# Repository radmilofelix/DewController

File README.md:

# DewController
 **Device to control the dew heaters and fans on astronomic instruments**
 
 Dew is an obvious nuisance for astronomic instruments and a simple way of getting rid of it are heaters placed on elements of the optical chain susceptible to forming dew.

The described device is a 6 channel heater driver, and a 2 channel fan driver, as some reflecting telescopes have a fan installed on the back of the main mirror.

The heaters and fans are driven by PWM signals software controlled by means of a STM32F103 microcontroller. The connection with the computer can be achieved either through USB or Ethernet (TCP/IP) or both.

The device also has a DHT22 temperature & humidity sensor, so the dew point can be computed to get an indication of whether the heaters have to be powered and how much power has to be supplied to the heaters.

# Description

1.  - Heater 1 (connector and LED)
2.  - Heater 2 (connector and LED)
3.  - Heater 3 (connector and LED)
4.  - Heater 4 (connector and LED)
5.  - Heater 5 (connector and LED)
6.  - Heater 6 (connector and LED)
7.  - USB connector
8.  - Ethernet Connector
9.  - Connector for servicing - 9 pin
10.  - Fan 1 (connector and LED)
11.  - Fan 2 (connector and LED)
12. - DHT 22 sensor
13. - 12V power connector
14. - Reset button
15. - Bracket for mounting the device on the telescope

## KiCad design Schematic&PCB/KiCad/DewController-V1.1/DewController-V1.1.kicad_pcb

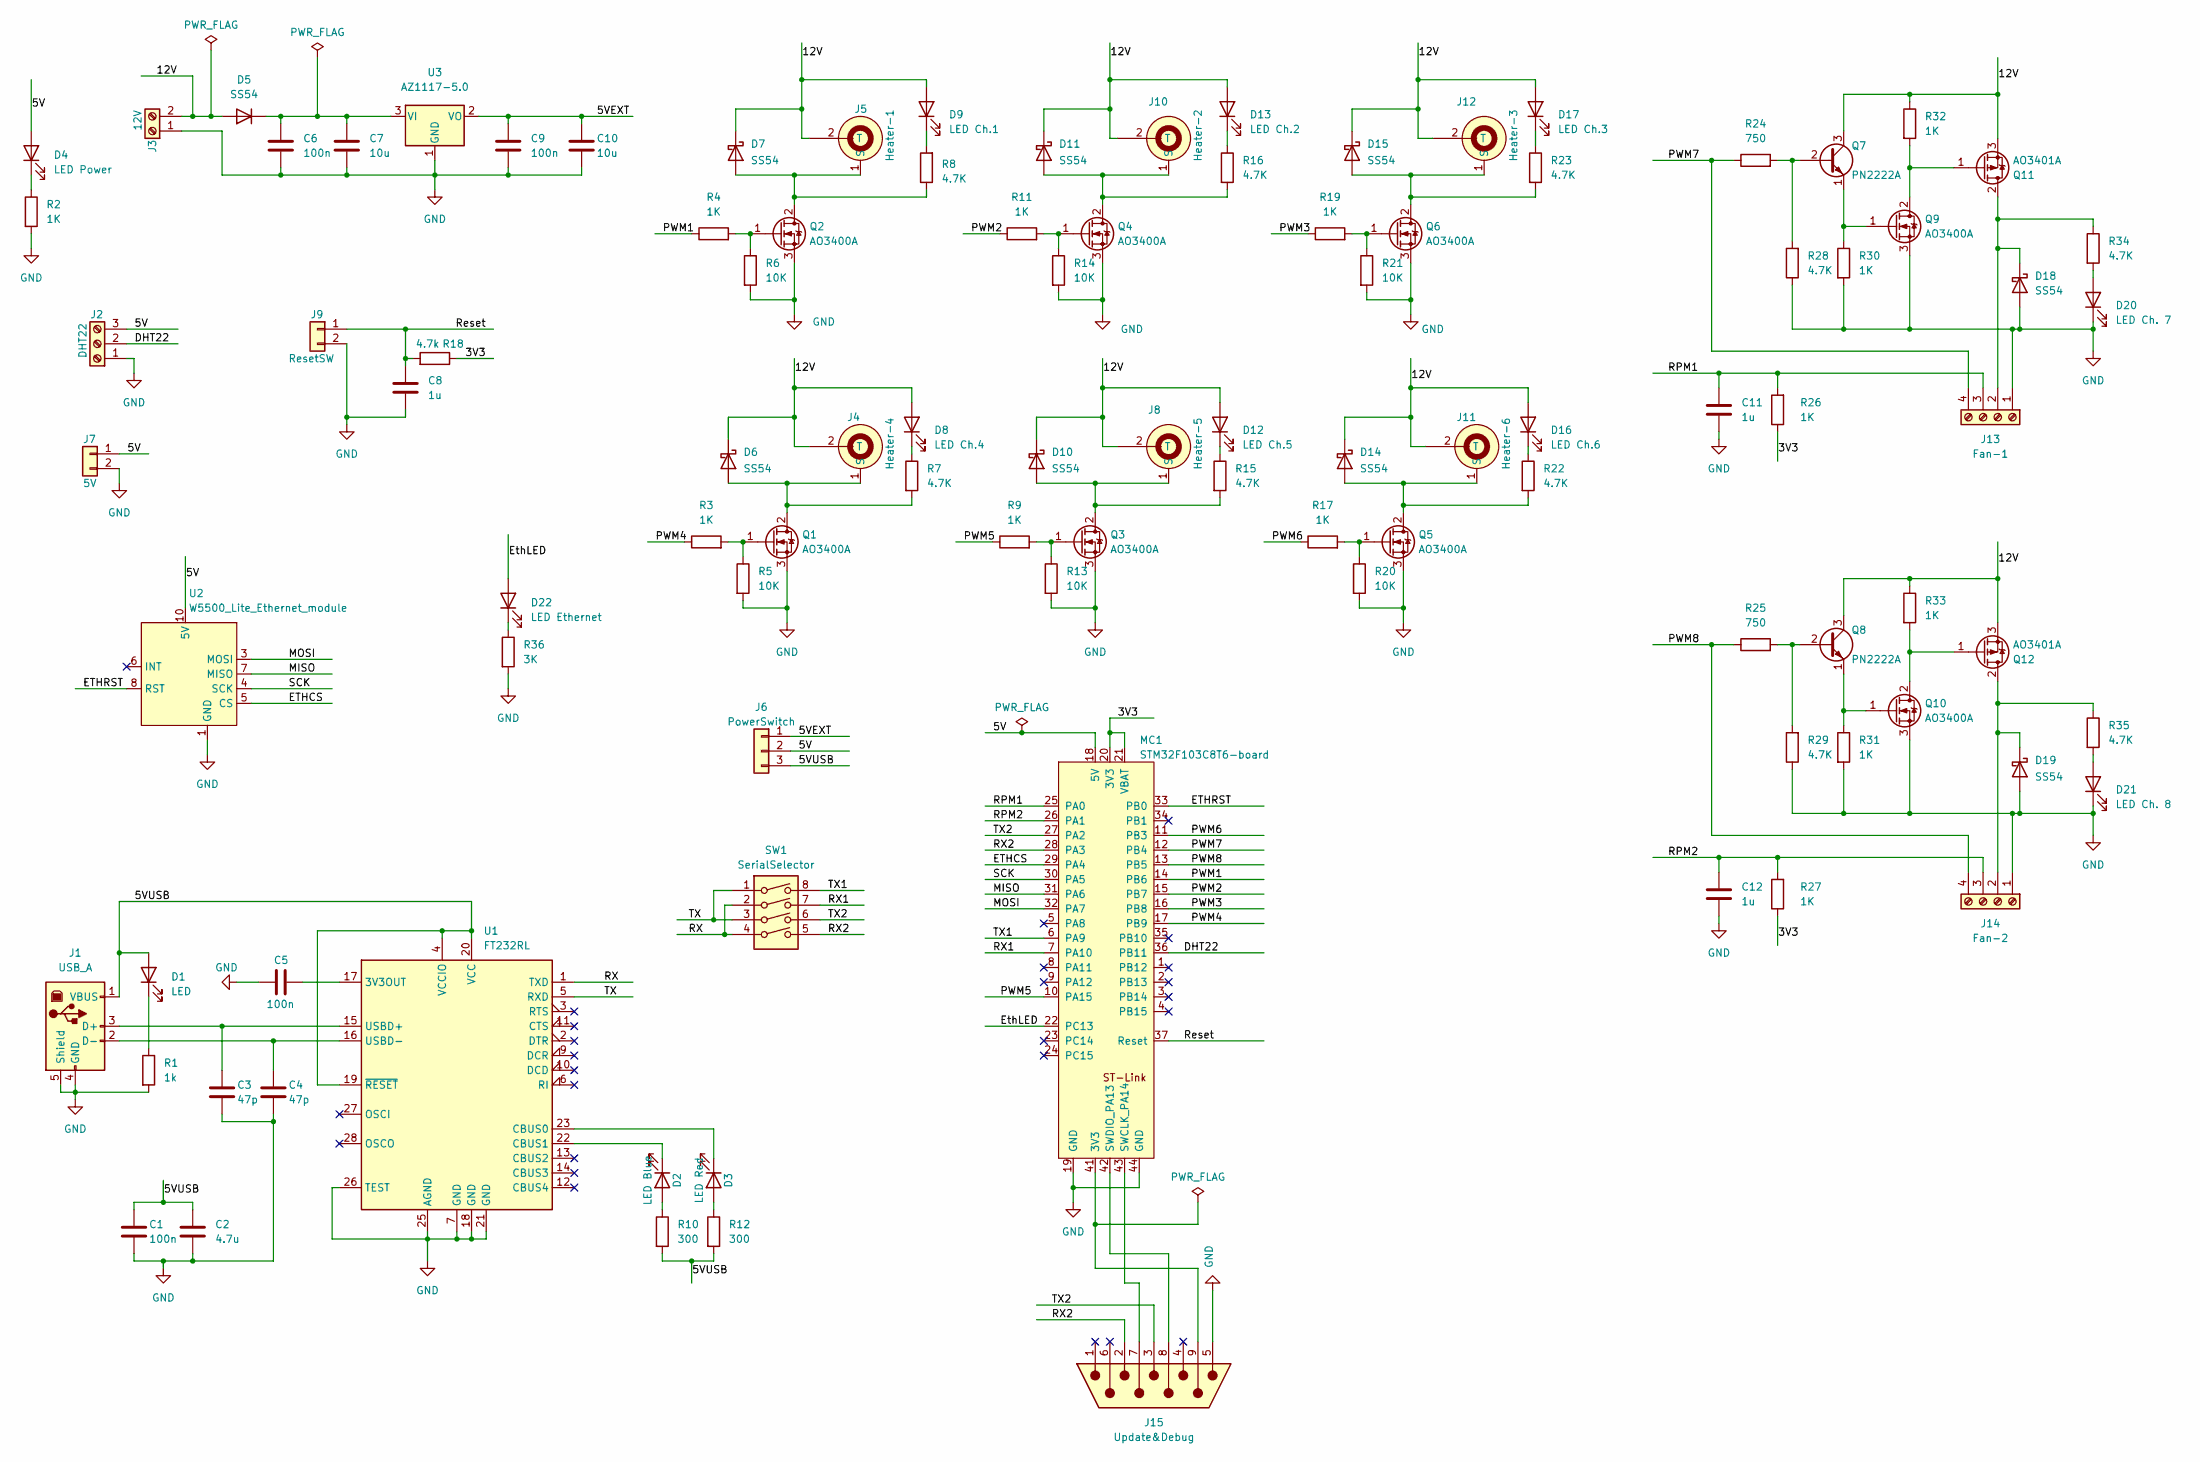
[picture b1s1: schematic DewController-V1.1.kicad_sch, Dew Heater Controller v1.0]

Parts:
C1, C5, C6, C9: 100n; C_0805_2012Metric; LCSC C49678
C2: 4.7u; CP_EIA-3528-21_Kemet-B; LCSC C1779
C3, C4: 47p; C_0805_2012Metric; LCSC C14857
C7, C10: 10u; CP_EIA-3528-21_Kemet-B; LCSC C140404
C8, C11, C12: 1u; C_0805_2012Metric; LCSC C28323
D1: LED; LED_0805_2012Metric; LCSC C84256
D2: LED Blue; LED_0603_1608Metric; LCSC C72038
D3: LED Red; LED_0603_1608Metric; LCSC C72043
D4: LED Power; LED_D5.0mm
D5, D6, D7, D10, D11, D14, D15, D18, D19: SS54; D_SMA; LCSC C22452
D8: LED Ch.4; LED_D5.0mm
D9: LED Ch.1; LED_D5.0mm
D12: LED Ch.5; LED_D5.0mm
D13: LED Ch.2; LED_D5.0mm
D16: LED Ch.6; LED_D5.0mm
D17: LED Ch.3; LED_D5.0mm
D20: LED Ch. 7; LED_D5.0mm
D21: LED Ch. 8; LED_D5.0mm
D22: LED Ethernet; LED_D5.0mm
J1: USB_A; USB_B_Lumberg_2411_02_Horizontal
J2: DHT22; TerminalBlock_PTR_AKZ950-3_P5.08mm_Vertical
J3: 12V; TerminalBlock_PTR_AKZ950-2_P5.08mm_Vertical
J4: Heater-4; RCA_F_4Pin_15mm_11mm
J5: Heater-1; RCA_F_4Pin_15mm_11mm
J6: PowerSwitch; PinHeader_1x03_P2.54mm_Vertical
J7: 5V; PinHeader_1x02_P2.54mm_Vertical
J8: Heater-5; RCA_F_4Pin_15mm_11mm
J9: ResetSW; PinHeader_1x02_P2.54mm_Vertical
J10: Heater-2; RCA_F_4Pin_15mm_11mm
J11: Heater-6; RCA_F_4Pin_15mm_11mm
J12: Heater-3; RCA_F_4Pin_15mm_11mm
J13: Fan-1; TerminalBlock_PTR_AKZ950-4_P5.08mm_Vertical
J14: Fan-2; TerminalBlock_PTR_AKZ950-4_P5.08mm_Vertical
J15: Update&Debug; DSUB-9_Male_Horizontal_P2.77x2.84mm_EdgePinOffset4.94mm_Hou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
MC1: STM32F103C8T6-board; STM32F103C8T6
Q1, Q2, Q3, Q4, Q5, Q6, Q9, Q10: AO3400A; SOT-23-3-DS-inv; LCSC C20917
Q7, Q8: PN2222A; TO-92_Inline
Q11, Q12: AO3401A; SOT-23-DS-inv; LCSC C15127
R1: 1k; R_1206_3216Metric; LCSC C4410
R2, R3, R4, R9, R11, R17, R19, R26, R27, R30, R31, R32, R33: 1K; R_1206_3216Metric; LCSC C4410
R5, R6, R13, R14, R20, R21: 10K; R_1206_3216Metric; LCSC C17902
R7, R8, R15, R16, R22, R23, R28, R29, R34, R35: 4.7K; R_1206_3216Metric; LCSC C17936
R10, R12: 300; R_1206_3216Metric; LCSC C17887
R18: 4.7k; R_1206_3216Metric; LCSC C17936
R24, R25: 750; R_1206_3216Metric; LCSC C17985
R36: 3K; R_1206_3216Metric; LCSC C17944
SW1: SerialSelector; DIP-8_W7.62mm
U1: FT232RL; SSOP-28_5.3x10.2mm_P0.65mm; LCSC C8690
U2: W5500_Lite_Ethernet_module; W5500_Lite
U3: AZ1117-5.0; SOT-223; LCSC C6187

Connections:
/3V3: MC1.20 (3V3), MC1.21 (VBAT), MC1.38 (3V3), R18.1, R26.1, R27.1
/5V: D4.2 (A), J2.3, J6.2, J7.1, MC1.18 (5V), U2.10 (5V), U2.11 (5V)
/5VEXT: C9.1, C10.1, J6.1, U3.2 (VO)
/5VUSB: C1.1, C2.1, D1.2 (A), J1.1 (VBUS), J6.3, R10.2, R12.2, U1.4 (VCCIO), U1.19 (~RESET), U1.20 (VCC)
/12V: D5.2 (A), D6.1 (K), D7.1 (K), D8.2 (A), D9.2 (A), D10.1 (K), D11.1 (K), D12.2 (A), D13.2 (A), D14.1 (K), D15.1 (K), D16.2 (A), D17.2 (A), J3.2, J4.2 (T), J5.2 (T), J8.2 (T), J10.2 (T), J11.2 (T), J12.2 (T), Q7.3 (C), Q8.3 (C), Q11.3 (S), Q12.3 (S), R32.1, R33.1
/DHT22: J2.2, MC1.36 (PB11)
/ETHCS: MC1.29 (PA4), U2.5 (CS)
/ETHRST: MC1.33 (PB0), U2.8 (RST)
/EthLED: D22.2 (A), MC1.22 (PC13)
/MISO: MC1.31 (PA6), U2.7 (MISO)
/MOSI: MC1.32 (PA7), U2.3 (MOSI)
/PWM1: MC1.14 (PB6), R4.1
/PWM2: MC1.15 (PB7), R11.1
/PWM3: MC1.16 (PB8), R19.1
/PWM4: MC1.17 (PB9), R3.1
/PWM5: MC1.10 (PA15), R9.1
/PWM6: MC1.11 (PB3), R17.1
/PWM7: J13.4, MC1.12 (PB4), R24.1
/PWM8: J14.4, MC1.13 (PB5), R25.1
/RPM1: C11.1, J13.3, MC1.25 (PA0), R26.2
/RPM2: C12.1, J14.3, MC1.26 (PA1), R27.2
/RX: SW1.2, SW1.4, U1.1 (TXD)
/RX1: MC1.7 (PA10), SW1.7
/RX2: J15.2, MC1.28 (PA3), SW1.5
/Reset: C8.1, J9.1, MC1.37 (Reset), R18.2
/SCK: MC1.30 (PA5), U2.4 (SCK)
/TX: SW1.1, SW1.3, U1.5 (RXD)
/TX1: MC1.6 (PA9), SW1.8
/TX2: J15.3, MC1.27 (PA2), SW1.6
GND: C1.2, C2.2, C3.2, C4.2, C5.2, C6.2, C7.2, C8.2, C9.2, C10.2, C11.2, C12.2, D18.2 (A), D19.2 (A), D20.1 (K), D21.1 (K), J1.4 (GND), J1.5 (Shield), J2.1, J3.1, J7.2, J9.2, J13.1, J14.1, J15.5, MC1.19 (GND), MC1.39 (GND), MC1.40 (GND), MC1.44 (GND), Q1.3 (S), Q2.3 (S), Q3.3 (S), Q4.3 (S), Q5.3 (S), Q6.3 (S), Q9.3 (S), Q10.3 (S), R1.2, R2.2, R5.2, R6.2, R13.2, R14.2, R20.2, R21.2, R28.1, R29.1, R30.2, R31.2, R36.2, U1.7 (GND), U1.18 (GND), U1.21 (GND), U1.25 (AGND), U1.26 (TEST), U2.1 (GND), U2.2 (GND), U2.12 (GND), U3.1 (GND)
unnamed: D1.1 (K), R1.1
unnamed: D2.2 (A), R10.1
unnamed: D2.1 (K), U1.22 (CBUS1)
unnamed: D3.2 (A), R12.1
unnamed: D3.1 (K), U1.23 (CBUS0)
unnamed: D4.1 (K), R2.1
unnamed: C6.1, C7.1, D5.1 (K), U3.3 (VI)
unnamed: D6.2 (A), J4.1 (S), J4.3 (S), J4.4 (S), Q1.2 (D), R7.2
unnamed: D7.2 (A), J5.1 (S), J5.3 (S), J5.4 (S), Q2.2 (D), R8.1
unnamed: D8.1 (K), R7.1
unnamed: D9.1 (K), R8.2
unnamed: D10.2 (A), J8.1 (S), J8.3 (S), J8.4 (S), Q3.2 (D), R15.2
unnamed: D11.2 (A), J10.1 (S), J10.3 (S), J10.4 (S), Q4.2 (D), R16.2
unnamed: D12.1 (K), R15.1
unnamed: D13.1 (K), R16.1
unnamed: D14.2 (A), J11.1 (S), J11.3 (S), J11.4 (S), Q5.2 (D), R22.2
unnamed: D15.2 (A), J12.1 (S), J12.3 (S), J12.4 (S), Q6.2 (D), R23.2
unnamed: D16.1 (K), R22.1
unnamed: D17.1 (K), R23.1
unnamed: D18.1 (K), J13.2, Q11.2 (D), R34.1
unnamed: D19.1 (K), J14.2, Q12.2 (D), R35.1
unnamed: D20.2 (A), R34.2
unnamed: D21.2 (A), R35.2
unnamed: D22.1 (K), R36.1
unnamed: C3.1, J1.3 (D+), U1.15 (USBD+)
unnamed: C4.1, J1.2 (D-), U1.16 (USBD-)
unnamed: J15.9, MC1.41 (3V3)
unnamed: J15.7, MC1.43 (SWCLK_PA14)
unnamed: J15.8, MC1.42 (SWDIO_PA13)
unnamed: Q1.1 (G), R3.2, R5.1
unnamed: Q2.1 (G), R4.2, R6.1
unnamed: Q3.1 (G), R9.2, R13.1
unnamed: Q4.1 (G), R11.2, R14.1
unnamed: Q5.1 (G), R17.2, R20.1
unnamed: Q6.1 (G), R19.2, R21.1
unnamed: Q7.2 (B), R24.2, R28.2
unnamed: Q7.1 (E), Q9.1 (G), R30.1
unnamed: Q8.2 (B), R25.2, R29.2
unnamed: Q10.2 (D), Q12.1 (G), R33.2
unnamed: Q8.1 (E), Q10.1 (G), R31.1
unnamed: Q9.2 (D), Q11.1 (G), R32.2
unnamed: C5.1, U1.17 (3V3OUT)

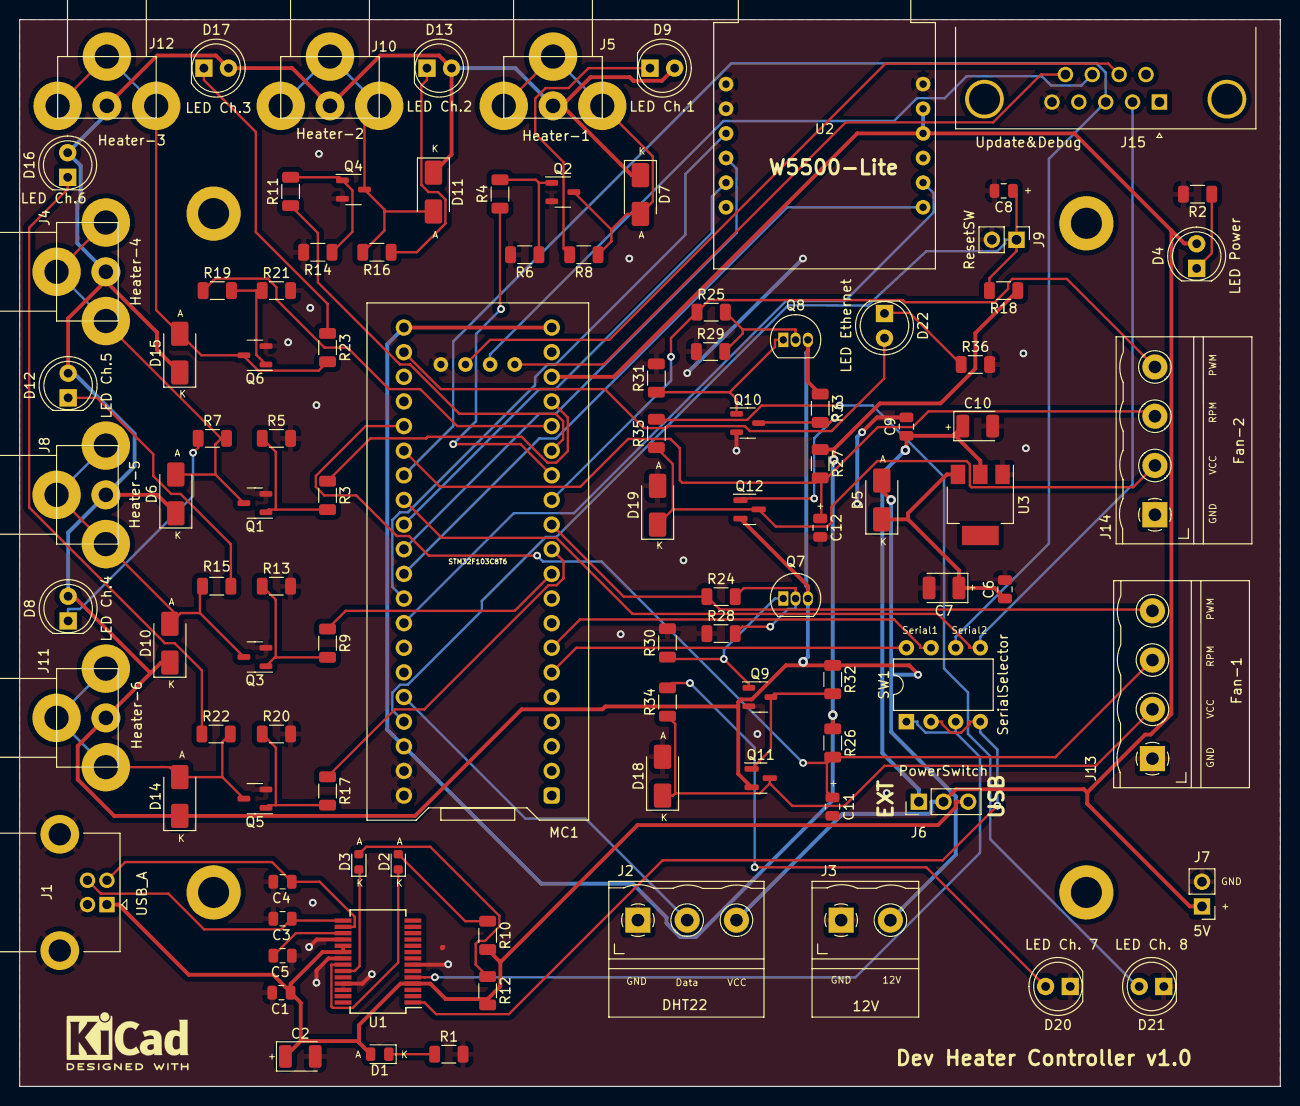
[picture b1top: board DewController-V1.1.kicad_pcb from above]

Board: 2 copper layers, 130.0 x 110.0 mm, 106 parts (0 on the bottom side), 72 nets.

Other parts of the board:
MH1, MH2, MH3, MH4: MountingHole_3.2mm_M3_DIN965_Pad

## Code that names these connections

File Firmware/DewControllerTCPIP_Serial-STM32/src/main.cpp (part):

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
#include "dewHeaterController.h"

#define RPMPIN1 PA0
#define RPMPIN2 PA1
#define MAGPOLES 2 // number of poles driving the Hall sensor
#define ETHLED PC13

#define DHTPIN PB11
#define DHTTYPE DHT22 // DHT 22  (AM2302), AM2321
long rpm = 0;
int speed = 9999;
DHT dhtSensor(DHTPIN,DHTTYPE);
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void setup()
{
    dhtSensor.begin();
    pwmPin[0] = PB6;
    pwmPin[1] = PB7;
    pwmPin[2] = PB8;
    pwmPin[3] = PB3;
    pwmPin[4] = PA15;
    pwmPin[5] = PB9;
    pwmPin[6] = PB4;
    pwmPin[7] = PB5;

    analogWriteFrequency(25000); // set PWM frequency - all timers - to 25KHz (default is 1kHz)
//  analogWriteFrequency(8000); // set PWM frequency - all timers - to 8KHz (default is 1kHz)
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    delay(300);

//  switch off ETH LED
    pinMode(ETHLED, OUTPUT);
    digitalWrite(ETHLED, LOW);

  // Open serial communications and wait for port to open:
//  Serial2.begin(19200);  // PA3  (RX)  PA2  (TX)
    Serial.begin(115200);  // PA10  (RX)  PA9  (TX)
    Serial.setTimeout(500);
//  Serial.setTimeout(3000);
#ifdef DEBUG
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
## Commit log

2023-07-04 Added PC client
2023-07-04 Work in progress
2023-07-05 Work on client UI
    Controls arrangement and enable conditions
2023-07-09 Work on PC Client
2023-07-15 current work
2023-08-17 Comm services splitted into classes
2023-08-17 Cleanup
2023-08-17 updat
2023-08-17 cosmetic adjustments
2023-08-18 Changed MAC address
2023-08-19 Unique MAC addresses to devices
2023-10-13 finished the INDI driver
2023-10-13 added DHCP option in firmware
2023-10-18 readme update
2023-10-31 updated .gitignore
2024-02-08 Correct heaters numbers
2024-06-15 updated INDI driver to indilib 2.8.0
2025-06-19 Code was adapted for the new INDI library v2.1.4, CMakeLists.txt optimised
2026-03-17 Location update
